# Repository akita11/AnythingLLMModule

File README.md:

# AnythingLLM Module

M5Stack Coreシリーズに接続し、他のPC等で動作しているAIモデル（大規模言語モデル(LLM)）を、M5Stackから使用できるようにするModuleです。M5Stackとは、M5Stack社のLLM Moduleと同等の接続となるため、ソフトウエア的にはLLM Moduleと同様に扱うことができます。他のPCのLLMへはUSBやWiFiで接続します。M5StampS3Aに必要なソフトウエアを書き込んで使用してください。StampS3Aの取り付け方法が2種類あります。

## StampS3Aを直接とりつけ

[StampS3A](https://www.switch-science.com/products/10377)をリフローはんだ付け等で直接基板に実装します。M5Stack接続用のMbusコネクタもリフローはんだ付け等で基板に実装してください。また必要に応じて、Module Frameをとりつけてください。

## StampS3Aをコネクタを介してとりつけ

[2.54mmピンヘッダ実装済みのStampS3A](https://www.switch-science.com/products/10734)と、6pと9p（または8p）のピンソケット、およびMbusコネクタまたは2.54mmの2列x15ピンの低プロファイルのピンヘッダを用意します。

まず基板のこちら面に、6pと9p（または8p）のピンソケットをはんだ付けします。8pソケットを使う場合は、この写真のように1列分を開けた位置にとりつけてください。

Mbusコネクタをはんだ付け、または2.54mmの2列x15ピンの低プロファイルのピンヘッダをこの写真のようにはんだ付けします。M5Stack本体に接続される側（この写真では下側）の端子の先端が、基板面から5.5mmの位置になるようにしてください。

最後に[2.54mmピンヘッダ実装済みのStampS3A](https://www.switch-science.com/products/10734)を取り付けて完成です。

## ソフトウエア

Moduleに書き込む専用のファームウェアがあります。CoreからはLLM-Moduleのライブラリで通信できるように **「一部」** なっています。PC等との通信はWiFiまたはシリアル通信が選択できます。

### Module側

**USB-Cコネクタを接続する時に、ハンダ付けが取れないように注意してください！！！**  
**はがれやすい場合があるので、かならずStampS3を手で押さえて抜き差しすること！！！**  

PlatformIOで[stampS3R](https://github.com/akita11/AnythingLLMModule/tree/main/stampS3R)をビルドして、基板上のM5StampS3に書き込みます。  
このとき、`secrets.h`でPC等のローカルIPアドレス、WiFiのSSID/パスワードを設定してください。  

### PC側

現在はLLMサーバーとしてOllamaのみサポートしています。  
シリアルで接続する場合は[serial](https://github.com/akita11/AnythingLLMModule/tree/main/serial)にあるスクリプトを動かして待機させてください。  
WiFiで接続する場合はOllamaの設定から`Expose Ollama to the network`を有効にしてください。  

### サンプル

サンプルプログラム([coreS3_test](https://github.com/akita11/AnythingLLMModule/tree/main/coreS3_test))を用意しています。お使いのOllamaからアクセス可能なモデル名に変更してお試しください。画面に`ready`と表示されたら、シリアルモニタからテキストを入力してEnterキーを押すと、会話ができます。

### API対応状況(2025/11/20)

- [o] module_llm.checkConnection
- [o] module_llm.llm.setup
- [o] module_llm.llm.inferenceAndWaitResult

## Author

Designed by Junichi Akita (@akita11) / akita@ifdl.jp  
Programmed by Ogawa3427 / ogawa3427@ifdl.jp

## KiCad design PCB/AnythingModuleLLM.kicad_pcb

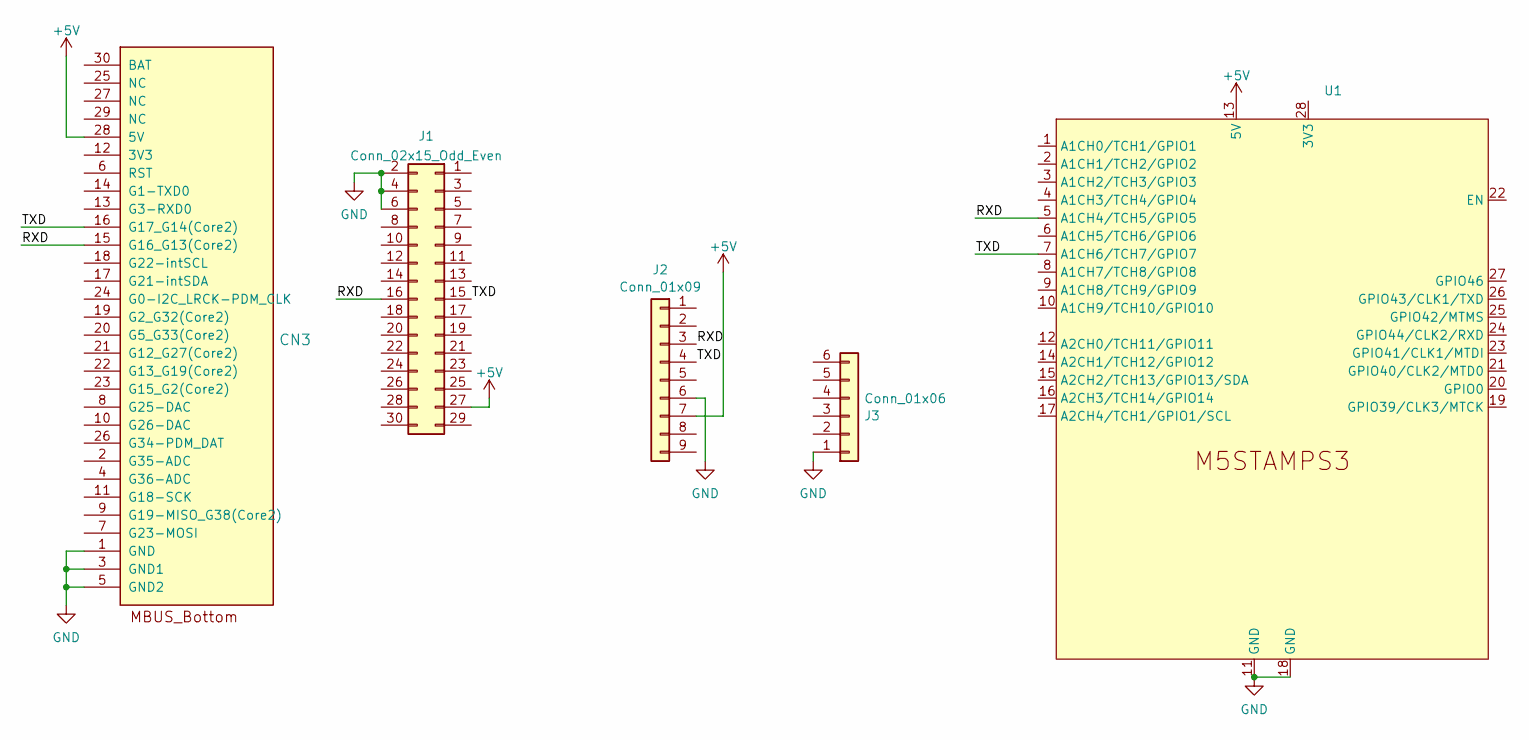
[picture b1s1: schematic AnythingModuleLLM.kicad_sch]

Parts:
CN3: CON_MBUS_bottom_Core2; M5STACK_BUS_30P
J1: Conn_02x15_Odd_Even; PinHeader_2x15_P2.54mm_Vertical
J2: Conn_01x09; PinHeader_1x09_P2.54mm_Vertical
J3: Conn_01x06; PinHeader_1x06_P2.54mm_Vertical
U1: STAMP-S3-SMD

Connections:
+5V: CN3.28 (5V), J1.27, J2.7, U1.13 (5V)
/RXD: CN3.15 (G16_G13(Core2)), J1.16, J2.3, U1.5 (A1CH4/TCH5/GPIO5)
/TXD: CN3.16 (G17_G14(Core2)), J1.15, J2.4, U1.7 (A1CH6/TCH7/GPIO7)
GND: CN3.1 (GND), CN3.3 (GND1), CN3.5 (GND2), J1.2, J1.4, J1.6, J2.6, J3.1, U1.11 (GND), U1.18 (GND)

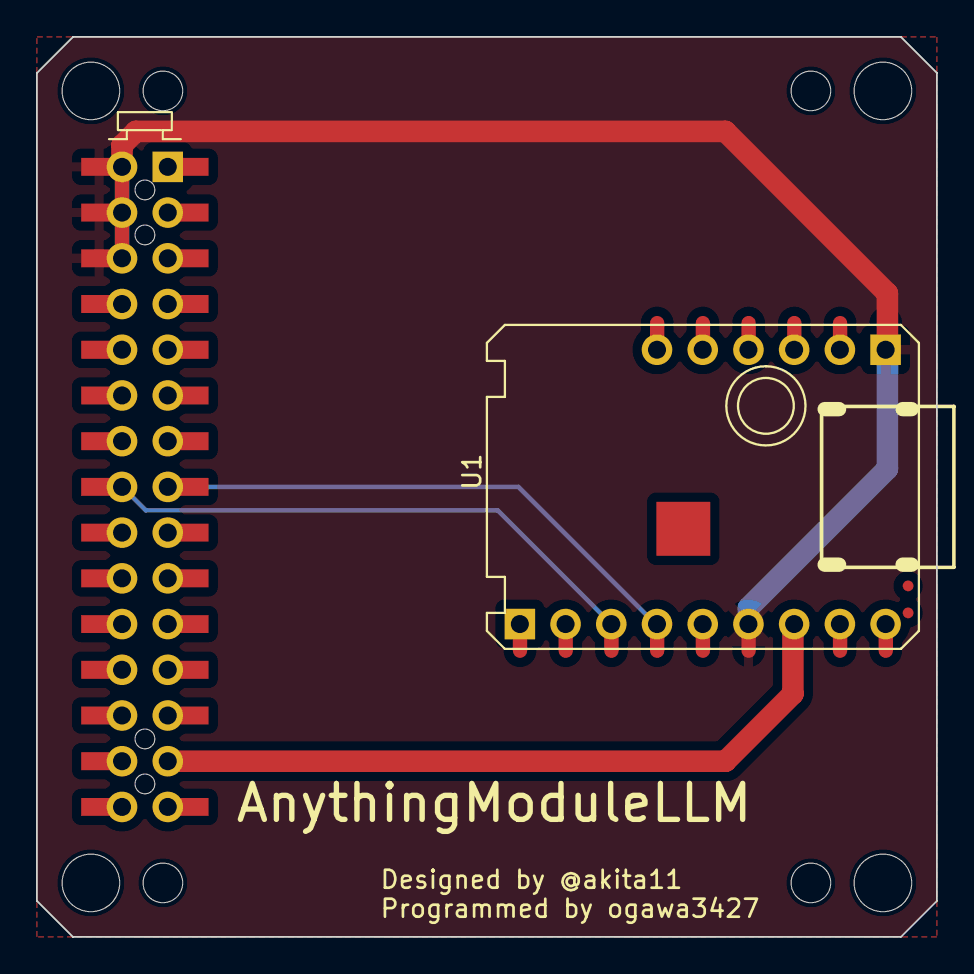
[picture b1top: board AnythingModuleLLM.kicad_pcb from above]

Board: 2 copper layers, 50.0 x 50.0 mm, 5 parts (1 on the bottom side), 4 nets.

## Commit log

2025-11-02 PCB folder
2025-11-06 wifi初期化関係
2025-11-06 長くなりそうなので複数ファイルに分割
2025-11-10 とりあえず何かの字が出る状態
2025-11-10 サンプルコードを追加
2025-11-12 add photos
2025-11-12 json関係をmainから排除
2025-11-12 update photo&README for parts
2025-11-12 secretsの雛形
2025-11-12 python追加_動かない可能性が高い
2025-11-12 READMEに追記
